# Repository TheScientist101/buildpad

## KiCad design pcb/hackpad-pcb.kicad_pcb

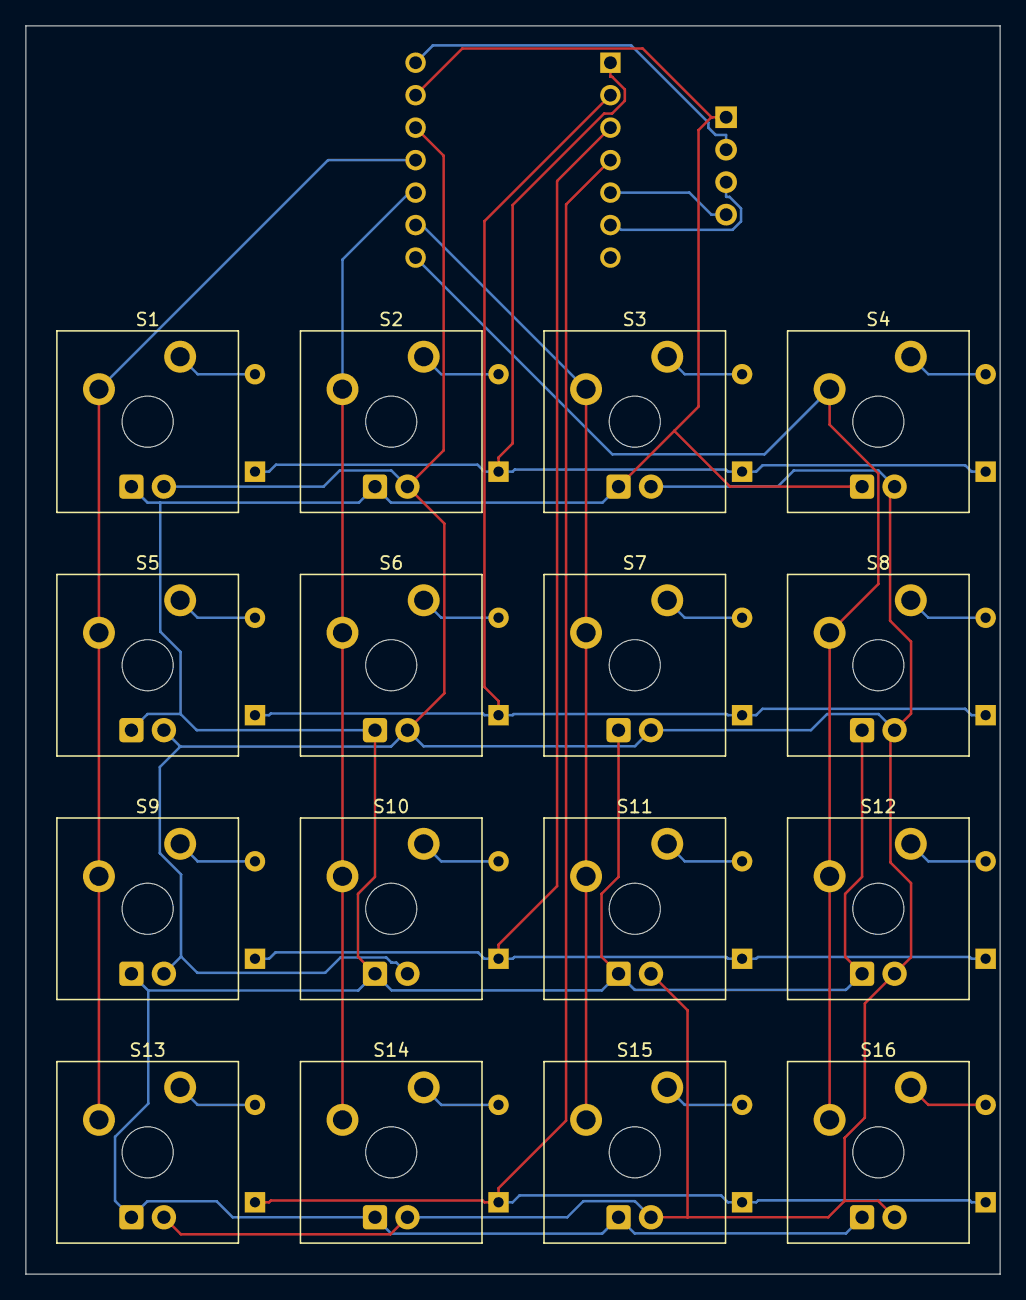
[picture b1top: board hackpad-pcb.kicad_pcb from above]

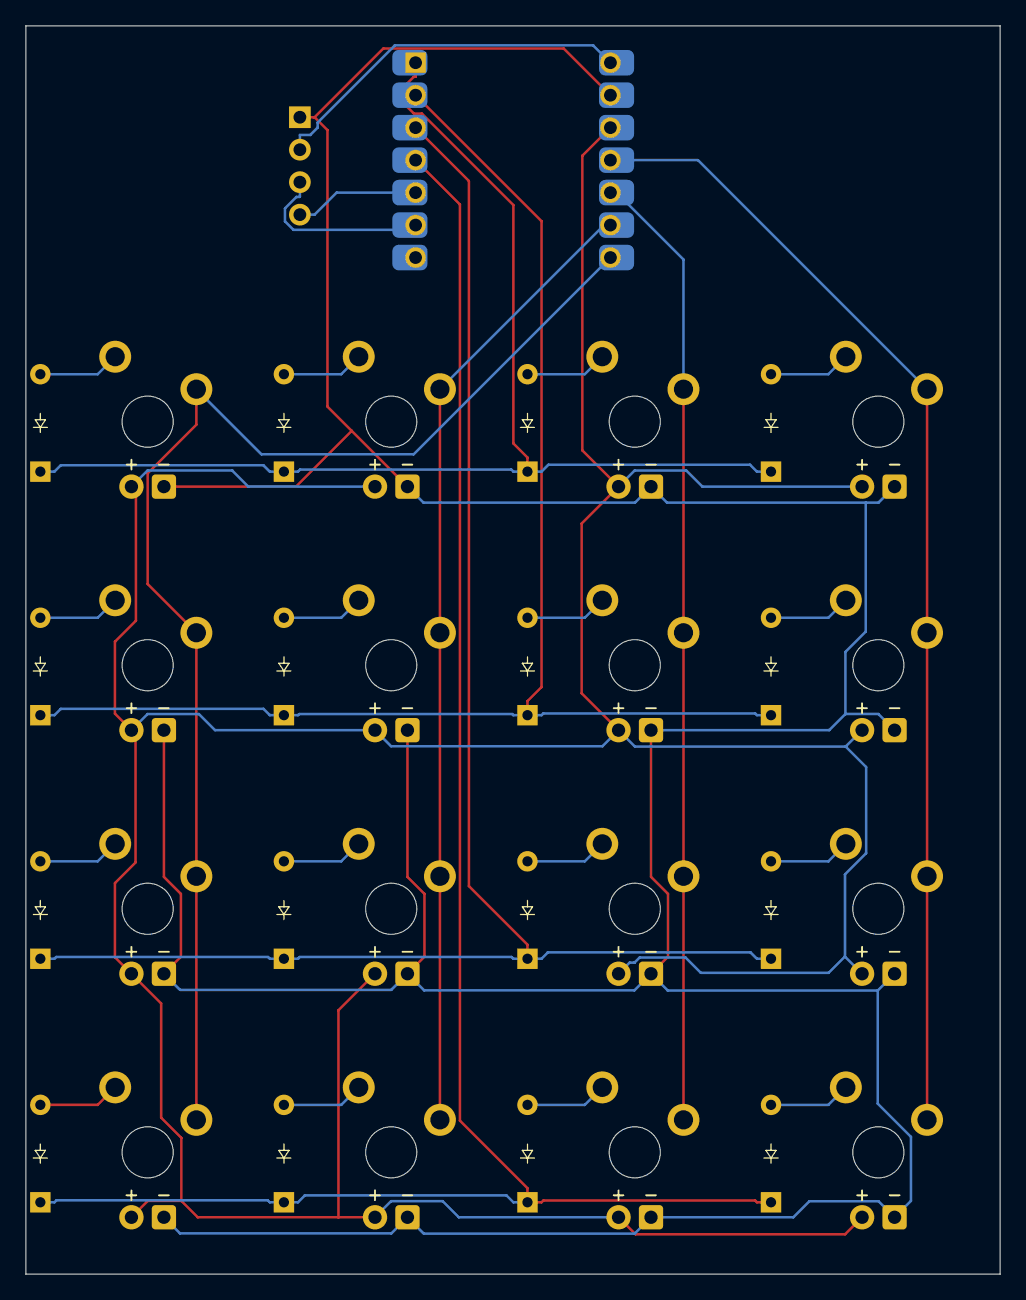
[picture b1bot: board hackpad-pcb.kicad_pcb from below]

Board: 2 copper layers, 76.2 x 97.6 mm, 50 parts (17 on the bottom side), 29 nets.

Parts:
D1, D2, D3, D4, D5, D6, D7, D8, D9, D10, D11, D12, D13, D14, D15, D16: Diode; Diode_DO-35
D17, D18, D19, D20, D21, D22, D23, D24, D25, D26, D27, D28, D29, D30, D31, D32: LED; LED_MX_3mm-ROT
J1: OLED_128x32
S1, S2, S3, S4, S5, S6, S7, S8, S9, S10, S11, S12, S13, S14, S15, S16: Keyswitch; MX_Plate_1.00u
U1: MCU_Seeed_XIAO_RP2040; Seeed_XIAO_RP2040

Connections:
+3V3: D17.2 (A), D18.2 (A), D19.2 (A), D20.2 (A), D21.2 (A), D22.2 (A), D23.2 (A), D24.2 (A), D25.2 (A), D26.2 (A), D27.2 (A), D28.2 (A), D29.2 (A), D30.2 (A), D31.2 (A), D32.2 (A), U1.12 (3V3)
/SCL: J1.3 (SCL), U1.6 (PA9_A5_D5_SCL)
/SDA: J1.4 (SDA), U1.5 (PA8_A4_D4_SDA)
Column 0: S1.1, S5.1, S9.1, S13.1, U1.11 (PA6_A10_D10_MOSI)
Column 1: S2.1, S6.1, S10.1, S14.1, U1.10 (PA5_A9_D9_MISO)
Column 2: S3.1, S7.1, S11.1, S15.1, U1.9 (PA7_A8_D8_SCK)
Column 3: S4.1, S8.1, S12.1, S16.1, U1.8 (PB09_A7_D7_RX)
GND: D17.1 (K), D18.1 (K), D19.1 (K), D20.1 (K), D21.1 (K), D22.1 (K), D23.1 (K), D24.1 (K), D25.1 (K), D26.1 (K), D27.1 (K), D28.1 (K), D29.1 (K), D30.1 (K), D31.1 (K), D32.1 (K), J1.1 (GND), U1.13 (GND)
unnamed: D1.2 (A), S1.2
unnamed: D2.2 (A), S2.2
unnamed: D3.2 (A), S3.2
unnamed: D4.2 (A), S4.2
unnamed: D5.2 (A), S5.2
unnamed: D6.2 (A), S6.2
unnamed: D7.2 (A), S7.2
unnamed: D8.2 (A), S8.2
unnamed: D9.2 (A), S9.2
unnamed: D10.2 (A), S10.2
unnamed: D11.2 (A), S11.2
unnamed: D12.2 (A), S12.2
unnamed: D13.2 (A), S13.2
unnamed: D14.2 (A), S14.2
unnamed: D15.2 (A), S15.2
unnamed: D16.2 (A), S16.2
Row 0: D1.1 (K), D2.1 (K), D3.1 (K), D4.1 (K), U1.1 (PA02_A0_D0)
Row 1: D5.1 (K), D6.1 (K), D7.1 (K), D8.1 (K), U1.2 (PA4_A1_D1)
Row 2: D9.1 (K), D10.1 (K), D11.1 (K), D12.1 (K), U1.3 (PA10_A2_D2)
Row 3: D13.1 (K), D14.1 (K), D15.1 (K), D16.1 (K), U1.4 (PA11_A3_D3)
VCC: J1.2 (VCC), U1.14 (5V)

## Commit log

2024-09-27 added submodules
2024-09-27 add footprint libraries
2024-09-28 Made schematic and routed wires
2024-09-28 Moved diodes and added OLED
2024-09-30 Routed a little bit more
2024-10-21 Replaced neopixels with simple 2x3x4 mm leds to avoid smd soldering
2024-10-21 Routed pcb using freerouter
2024-10-22 Completed case CAD
2024-10-23 Added keycaps to CAD and made firmware using kmk
2024-10-23 Resized pcb and updated model
2024-10-23 Added basic README
2024-10-24 Changed local label to global label
2024-10-25 Add resistors for LEDs
2025-12-29 probably should've pushed my qmk firmware
